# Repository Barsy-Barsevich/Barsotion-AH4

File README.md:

# AH4: ICM-45686 devboard
the 12th board after Berkut

---
## ⚡️Abstract
Development board for ICM-45686 InvenSense TDK gyroscope & accelerometer. You can connect to it's interfaces (AP, OIS, I2CM) or drive them by on-board CH32V305RBT6 microcontroller.

- All ICM-45686 interfaces are routed (AP, OIS, I2CM);
- AP interface can be I2C or SPI
- On-board 32.768 kHz quartz oscillator to stabilize ODR frequency;
- On-board 32-bit RISC-V MCU to simplify ICM-45686 research;
- USB 2.0 HS and USB-UART are routed from the MCU.

---
## ⚡️Continious progress
- [Previous board: Barsotion-TA](https://github.com/Barsy-Barsevich/Barsotion-TA)
- [Previous board: Barsotion-PL1](https://github.com/Barsy-Barsevich/Barsotion-PL1)

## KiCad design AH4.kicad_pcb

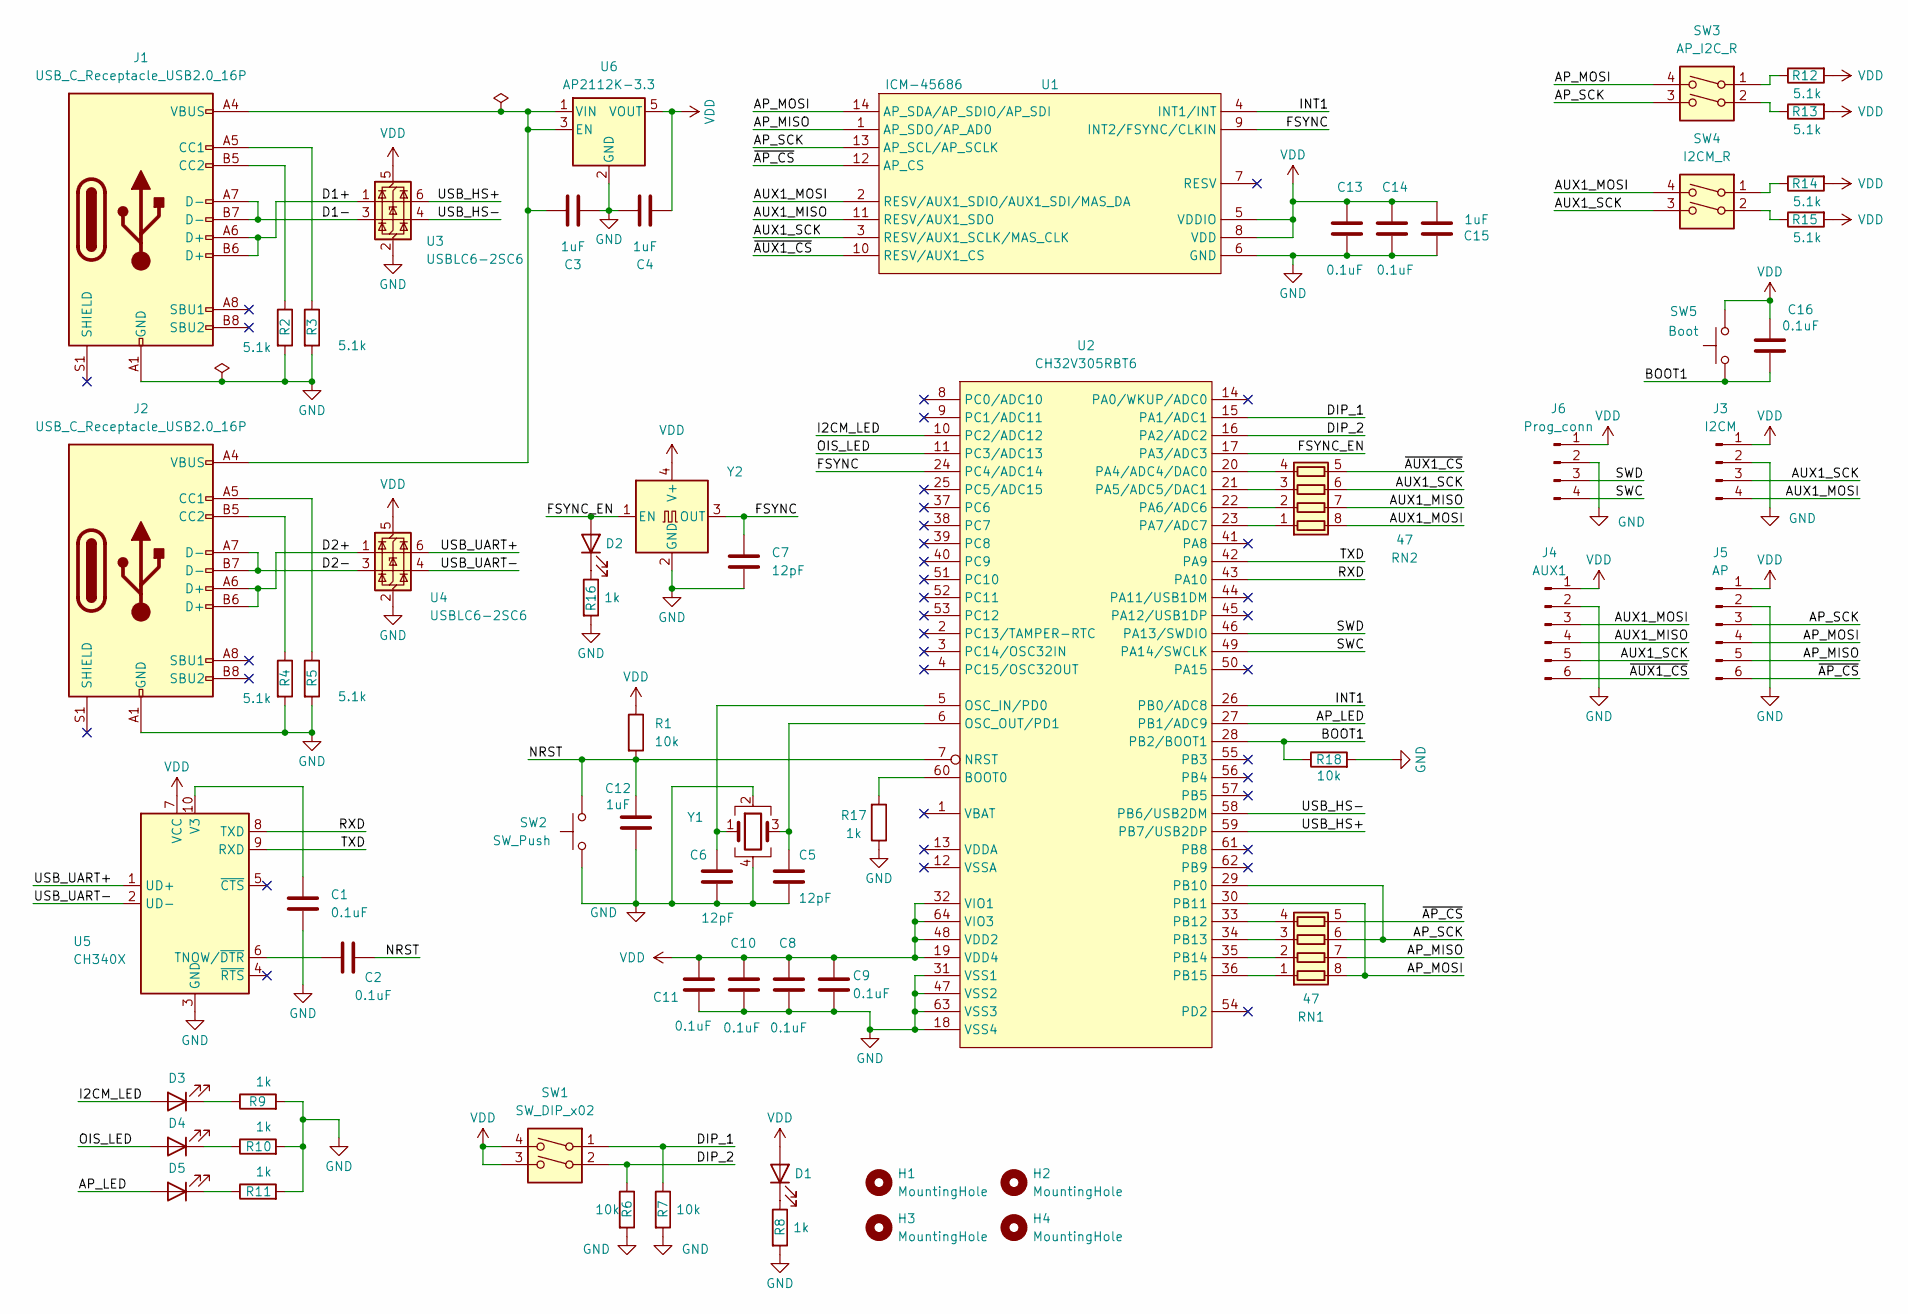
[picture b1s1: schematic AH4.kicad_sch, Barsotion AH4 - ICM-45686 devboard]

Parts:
C1, C2, C8, C9, C10, C11, C13, C14, C16: 0.1uF; C_0402_1005Metric
C3, C4, C12, C15: 1uF; C_0402_1005Metric
C5, C6, C7: 12pF; C_0402_1005Metric
D1, D2: Yellow LED; LED_0805_2012Metric
D3, D4, D5: Red LED; LED_0805_2012Metric
H1, H2, H3, H4: MountingHole; MountingHole_3.2mm_M3_Pad_Via
J1, J2: USB_C_Receptacle_USB2.0_16P; USB_C_Receptacle_GCT_USB4105-xx-A_16P_TopMnt_Horizontal; Mfr.Part TYPE C-DB-116PWB
J3: I2CM; PinHeader_1x04_P2.54mm_Vertical
J4: AUX1; PinHeader_1x06_P2.54mm_Vertical
J5: AP; PinHeader_1x06_P2.54mm_Vertical
J6: Prog_conn; PinHeader_1x04_P1.27mm_Vertical
R1, R6, R7, R18: 10k; R_0402_1005Metric
R2, R3, R4, R5, R12, R13, R14, R15: 5.1k; R_0402_1005Metric
R8, R9, R10, R11, R16, R17: 1k; R_0402_1005Metric
RN1, RN2: 47; R_Array_Convex_4x0402
SW1: SW_DIP_x02; SW_DIP_SPSTx02_Slide_Copal_CHS-02B_W7.62mm_P1.27mm; Mfr.Part CHS-02TB1
SW2: SW_Push; SW_Push_1P1T_NO_Vertical_Wuerth_434133025816; Mfr.Part TS3425BA
SW3: AP_I2C_R; SW_DIP_SPSTx02_Slide_Copal_CHS-02B_W7.62mm_P1.27mm; Mfr.Part CHS-02TB1
SW4: I2CM_R; SW_DIP_SPSTx02_Slide_Copal_CHS-02B_W7.62mm_P1.27mm; Mfr.Part CHS-02TB1
SW5: Boot; SW_Push_1P1T_NO_Vertical_Wuerth_434133025816; Mfr.Part TS3425BA
U1: ICM-45686; Mfr.Part ICM-45686
U2: CH32V305RBT6; LQFP-64_10x10mm_P0.5mm; Mfr.Part CH32V305RBT6
U3, U4: USBLC6-2SC6; SOT-23-6; Mfr.Part USBLC6-2SC6
U5: CH340X; MSOP-10_3x3mm_P0.5mm; Mfr.Part CH340X
U6: AP2112K-3.3; SOT-23-5; Mfr.Part AP2112K-3.3TRG1
Y1: Crystal_GND24; Crystal_SMD_2016-4Pin_2.0x1.6mm; Mfr.Part XL7EL89COI-111YLC-16M
Y2: Generator 32.768 kHz; Oscillator_SMD_EuroQuartz_XO32-4Pin_3.2x2.5mm; Mfr.Part OK7EL89CJI-111YLC-32.768K

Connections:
/AP_LED: D5.2 (A), U2.27 (PB1/ADC9)
/AP_MISO: J5.5, RN1.7 (R2.2), U1.1 (AP_SDO/AP_AD0)
/AP_MOSI: J5.4, RN1.8 (R1.2), SW3.4, U1.14 (AP_SDA/AP_SDIO/AP_SDI), U2.30 (PB11)
/AP_SCK: J5.3, RN1.6 (R3.2), SW3.3, U1.13 (AP_SCL/AP_SCLK), U2.29 (PB10)
/AUX1_MISO: J4.4, RN2.7 (R2.2), U1.11 (RESV/AUX1_SDO)
/AUX1_MOSI: J3.4, J4.3, RN2.8 (R1.2), SW4.4, U1.2 (RESV/AUX1_SDIO/AUX1_SDI/MAS_DA)
/AUX1_SCK: J3.3, J4.5, RN2.6 (R3.2), SW4.3, U1.3 (RESV/AUX1_SCLK/MAS_CLK)
/BOOT1: C16.2, R18.1, SW5.1, U2.28 (PB2/BOOT1)
/D1+: J1.A6 (D+), J1.B6 (D+), U3.1 (I/O1)
/D1-: J1.A7 (D-), J1.B7 (D-), U3.3 (I/O2)
/D2+: J2.A6 (D+), J2.B6 (D+), U4.1 (I/O1)
/D2-: J2.A7 (D-), J2.B7 (D-), U4.3 (I/O2)
/DIP_1: R7.1, SW1.1, U2.15 (PA1/ADC1)
/DIP_2: R6.1, SW1.2, U2.16 (PA2/ADC2)
/FSYNC: C7.1, U1.9 (INT2/FSYNC/CLKIN), U2.24 (PC4/ADC14), Y2.3 (OUT)
/FSYNC_EN: D2.2 (A), U2.17 (PA3/ADC3), Y2.1 (EN)
/I2CM_LED: D3.2 (A), U2.10 (PC2/ADC12)
/INT1: U1.4 (INT1/INT), U2.26 (PB0/ADC8)
/NRST: C2.2, C12.1, R1.2, SW2.2, U2.7 (NRST)
/OIS_LED: D4.2 (A), U2.11 (PC3/ADC13)
/RXD: U2.43 (PA10), U5.8 (TXD)
/SWC: J6.4, U2.49 (PA14/SWCLK)
/SWD: J6.3, U2.46 (PA13/SWDIO)
/TXD: U2.42 (PA9), U5.9 (RXD)
/USB_HS+: U2.59 (PB7/USB2DP), U3.6 (I/O1)
/USB_HS-: U2.58 (PB6/USB2DM), U3.4 (I/O2)
/USB_UART+: U4.6 (I/O1), U5.1 (UD+)
/USB_UART-: U4.4 (I/O2), U5.2 (UD-)
/~AP_CS: J5.6, RN1.5 (R4.2), U1.12 (AP_CS)
/~AUX1_CS: J4.6, RN2.5 (R4.2), U1.10 (RESV/AUX1_CS)
GND: C1.2, C3.2, C4.1, C5.2, C6.2, C7.2, C8.2, C9.2, C10.2, C11.2, C12.2, C13.2, C14.2, C15.1, J1.A1 (GND), J1.A12 (GND), J1.B1 (GND), J1.B12 (GND), J2.A1 (GND), J2.A12 (GND), J2.B1 (GND), J2.B12 (GND), J3.2, J4.2, J5.2, J6.2, R2.2, R3.2, R4.2, R5.2, R6.2, R7.2, R8.2, R9.2, R10.2, R11.2, R16.2, R17.1, R18.2, SW2.1, U1.6 (GND), U2.18 (VSS4), U2.31 (VSS1), U2.47 (VSS2), U2.63 (VSS3), U3.2 (GND), U4.2 (GND), U5.3 (GND), U6.2 (GND), Y1.2, Y1.4, Y2.2 (GND)
unnamed: D1.1 (K), R8.1
unnamed: D2.1 (K), R16.1
unnamed: D3.1 (K), R9.1
unnamed: D4.1 (K), R10.1
unnamed: D5.1 (K), R11.1
unnamed: J1.A5 (CC1), R3.1
unnamed: J1.B5 (CC2), R2.1
unnamed: J2.A5 (CC1), R5.1
unnamed: J2.B5 (CC2), R4.1
unnamed: R12.1, SW3.1
unnamed: R13.1, SW3.2
unnamed: R14.1, SW4.1
unnamed: R15.1, SW4.2
unnamed: RN1.1 (R1.1), U2.36 (PB15)
unnamed: RN1.2 (R2.1), U2.35 (PB14)
unnamed: RN1.3 (R3.1), U2.34 (PB13)
unnamed: RN1.4 (R4.1), U2.33 (PB12)
unnamed: RN2.1 (R1.1), U2.23 (PA7/ADC7)
unnamed: RN2.2 (R2.1), U2.22 (PA6/ADC6)
unnamed: RN2.3 (R3.1), U2.21 (PA5/ADC5/DAC1)
unnamed: RN2.4 (R4.1), U2.20 (PA4/ADC4/DAC0)
unnamed: R17.2, U2.60 (BOOT0)
unnamed: C6.1, U2.5 (OSC_IN/PD0), Y1.1
unnamed: C5.1, U2.6 (OSC_OUT/PD1), Y1.3
unnamed: C2.1, U5.6 (TNOW/~DTR)
unnamed: C1.1, U5.10 (V3)
unnamed: C3.1, J1.A4 (VBUS), J1.A9 (VBUS), J1.B4 (VBUS), J1.B9 (VBUS), J2.A4 (VBUS), J2.A9 (VBUS), J2.B4 (VBUS), J2.B9 (VBUS), U6.1 (VIN), U6.3 (EN)
VDD: C4.2, C8.1, C9.1, C10.1, C11.1, C13.1, C14.1, C15.2, C16.1, D1.2 (A), J3.1, J4.1, J5.1, J6.1, R1.1, R12.2, R13.2, R14.2, R15.2, SW1.3, SW1.4, SW5.2, U1.5 (VDDIO), U1.8 (VDD), U2.19 (VDD4), U2.32 (VIO1), U2.48 (VDD2), U2.64 (VIO3), U3.5 (VBUS), U4.5 (VBUS), U5.7 (VCC), U6.5 (VOUT), Y2.4 (V+)

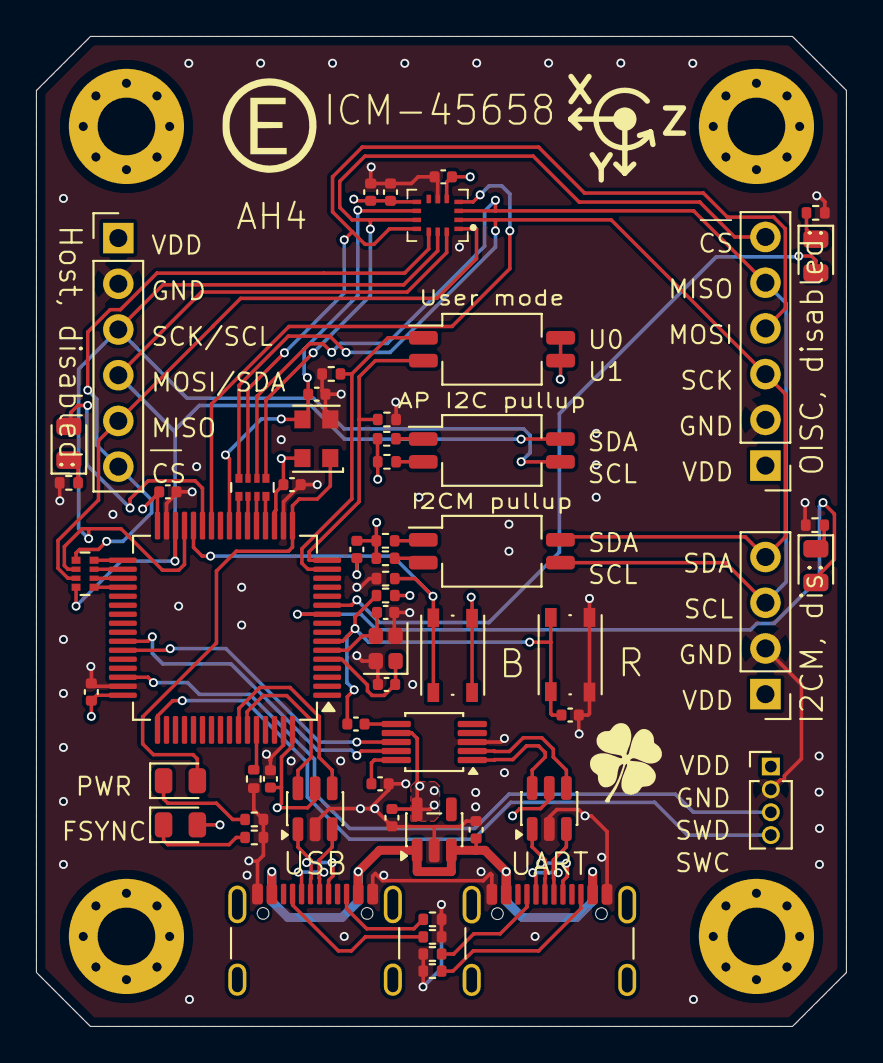
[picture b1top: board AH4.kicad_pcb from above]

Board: 4 copper layers, 45.0 x 55.0 mm, 64 parts (0 on the bottom side), 59 nets.

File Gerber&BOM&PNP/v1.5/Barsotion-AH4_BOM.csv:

Reference;Value;Datasheet;Footprint;Qty;Mfr.Part;Description
C1,C2,C8,C9,C10,C11,C13,C14,C16;0.1uF;~;Capacitor_SMD:C_0402_1005Metric;9;;Unpolarized capacitor
C3,C4,C12,C15;1uF;~;Capacitor_SMD:C_0402_1005Metric;4;;Unpolarized capacitor
C5,C6,C7;12pF;~;Capacitor_SMD:C_0402_1005Metric;3;;Unpolarized capacitor
D1,D2;Yellow LED;~;LED_SMD:LED_0805_2012Metric;2;;Light emitting diode, yellow 0805
D3,D4,D5;Red LED;~;LED_SMD:LED_0805_2012Metric;3;;Light emitting diode, red 0805
J1,J2;USB_C_Receptacle_USB2.0_16P;https://www.usb.org/sites/default/files/documents/usb_type-c.zip;Connector_USB:USB_C_Receptacle_GCT_USB4105-xx-A_16P_TopMnt_Horizontal;2;TYPE C-DB-116PWB;USB 2.0-only 16P Type-C Receptacle connector
R1,R6,R7,R18;10k;~;Resistor_SMD:R_0402_1005Metric;4;;Resistor
R2,R3,R4,R5,R12,R13,R14,R15;5.1k;~;Resistor_SMD:R_0402_1005Metric;8;;Resistor
R8,R9,R10,R11;1.5k;~;Resistor_SMD:R_0402_1005Metric;4;;Resistor
R16,R17;1k;~;Resistor_SMD:R_0402_1005Metric;2;;Resistor
RN1,RN2;47;~;Resistor_SMD:R_Array_Convex_4x0402;2;;4 resistor network, parallel topology
SW1;SW_DIP_x02;~;Button_Switch_SMD:SW_DIP_SPSTx02_Slide_Copal_CHS-02B_W7.62mm_P1.27mm;1;CHS-02TB1 ;2x DIP Switch, Single Pole Single Throw (SPST) switch, small symbol
SW2;SW_Push;~;Button_Switch_SMD:SW_Push_1P1T_NO_Vertical_Wuerth_434133025816;1;TS3425BA;Push button switch, generic, two pins
SW3;AP_I2C_R;~;Button_Switch_SMD:SW_DIP_SPSTx02_Slide_Copal_CHS-02B_W7.62mm_P1.27mm;1;CHS-02TB1 ;2x DIP Switch, Single Pole Single Throw (SPST) switch, small symbol
SW4;I2CM_R;~;Button_Switch_SMD:SW_DIP_SPSTx02_Slide_Copal_CHS-02B_W7.62mm_P1.27mm;1;CHS-02TB1 ;2x DIP Switch, Single Pole Single Throw (SPST) switch, small symbol
SW5;Boot;~;Button_Switch_SMD:SW_Push_1P1T_NO_Vertical_Wuerth_434133025816;1;TS3425BA;Push button switch, generic, two pins
U1;ICM-45686;;CustomPackage:ICM-45686;1;ICM-45686;Inertial measurement unit
U2;CH32V305RBT6;;Package_QFP:LQFP-64_10x10mm_P0.5mm;1;CH32V305RBT6;RISC-V WCH MCU
U3,U4;USBLC6-2SC6;https://www.st.com/resource/en/datasheet/usblc6-2.pdf;Package_TO_SOT_SMD:SOT-23-6;2;USBLC6-2SC6;Very low capacitance ESD protection diode, 2 data-line, SOT-23-6
U5;CH340X;https://cdn.sparkfun.com/assets/5/0/a/8/5/CH340DS1.PDF;Package_SO:MSOP-10_3x3mm_P0.5mm;1;CH340X;USB serial converter, 5V-tolerant IO, UART, MSOP-10
U6;AP2112K-3.3;https://www.diodes.com/assets/Datasheets/AP2112.pdf;Package_TO_SOT_SMD:SOT-23-5;1;AP2112K-3.3TRG1;600mA low dropout linear regulator, with enable pin, 3.8V-6V input voltage range, 3.3V fixed positive output, SOT-23-5
Y1;Crystal_GND24;~;Crystal:Crystal_SMD_2016-4Pin_2.0x1.6mm;1;XL7EL89COI-111YLC-16M;Four pin crystal, GND on pins 2 and 4
Y2;Generator 32.768 kHz;http://cdn-reichelt.de/documents/datenblatt/B400/XO32.pdf;Oscillator:Oscillator_SMD_EuroQuartz_XO32-4Pin_3.2x2.5mm;1;OK7EL89CJI-111YLC-32.768K;HCMOS Clock Oscillator

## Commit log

2025-07-13 init
2025-09-27 all kicad files included
2025-09-29 add kicad_prl & _pro files
2025-10-13 update, the board done
2025-10-14 update & gerber
2025-10-15 photos added
2025-10-15 readme update
2025-10-18 adding pictures
2025-11-23 update readme and photos
